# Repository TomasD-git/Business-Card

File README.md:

# Business-Card

> A custom dev board built inside a business card — NFC, e-paper display and 16 exposed GPIO pins.

---

## Features

- E-paper display — Configure once image stays
- NFC — tap to share Contact info, a URL, or any custom NFC
- 16 exposed GPIO pins — Connector makes it easy to use for another project
- No power design - Once flashed and configured, nfc works with no external power and image stays on e-paper screen

---

## How It Works

The Business Card is a fully custom PCB designed. The microcontroller drives both the e-paper display and the NFC IC over SPI/I2C, while the 16 GPIO pins are broken out along one edge for easy prototyping.

On power-up, the firmware initialises the display and NFC tag, can be configured, the e-paper holds whatever was last written without needing a continuous refresh.

---

## Schematic Overview

The schematic is split into four main blocks:

**MCU**: Core microcontroller, configuration of nfc and e-paper, GPIO pins   
**E-paper interface**: Has 8 exposed pins to solder an E-paper onto the PCB  
**NFC**: NFC IC with antenna matching network, presents as a standard NDEF tag  
**Power**: Power regulation with decoupling  

---

## PCB

Designed in KiCad, manufactured as a standard 2-layer board with PCBA. Gerber files and BOM are in the repo if you want to order your own.

---

<details>
  <summary>BOM</summary>

| Name | Purpose | Quantity | Total Cost (USD) | Link | Distributor |
|------|---------|----------|-----------------|------|-------------|
| locknut | secures the screen in place with M2 bolts | 1 | 4.88 | [Link](https://www.aliexpress.com/item/32963044301.html) | Aliexpress |
| PCB + PCBA | PCB with PCBA | 2 | 73.27 | [Link](https://jlcpcb.com) | jlcpcb |
| E-Paper, 2.13" | Screen to see my name | 1 | 12.44 | [Link](https://www.aliexpress.com/item/1005005183232092.html) | Aliexpress |

</details>

<details>
  <summary>For Future</summary>

## Planned improvements

**User interface**    
Change firmware so it could be configured with web or custom application.  

**Custom CAD**  
Some type of CAD to protect mcu.  

</details>

<details>
  <summary>License</summary>

### MIT License

**Copyright (c) [2026] [TomasD-git]**

Permission is hereby granted, free of charge, to any person obtaining a copy
of this software and associated documentation files (the "Software"), to deal
in the Software without restriction, including without limitation the rights
to use, copy, modify, merge, publish, distribute, sublicense, and/or sell
copies of the Software, and to permit persons to whom the Software is
furnished to do so, subject to the following conditions:

The above copyright notice and this permission notice shall be included in all
copies or substantial portions of the Software.

THE SOFTWARE IS PROVIDED "AS IS", WITHOUT WARRANTY OF ANY KIND, EXPRESS OR
IMPLIED, INCLUDING BUT NOT LIMITED TO THE WARRANTIES OF MERCHANTABILITY,
FITNESS FOR A PARTICULAR PURPOSE AND NONINFRINGEMENT. IN NO EVENT SHALL THE
AUTHORS OR COPYRIGHT HOLDERS BE LIABLE FOR ANY CLAIM, DAMAGES OR OTHER
LIABILITY, WHETHER IN AN ACTION OF CONTRACT, TORT OR OTHERWISE, ARISING FROM,
OUT OF OR IN CONNECTION WITH THE SOFTWARE OR THE USE OR OTHER DEALINGS IN THE
SOFTWARE.

</details>

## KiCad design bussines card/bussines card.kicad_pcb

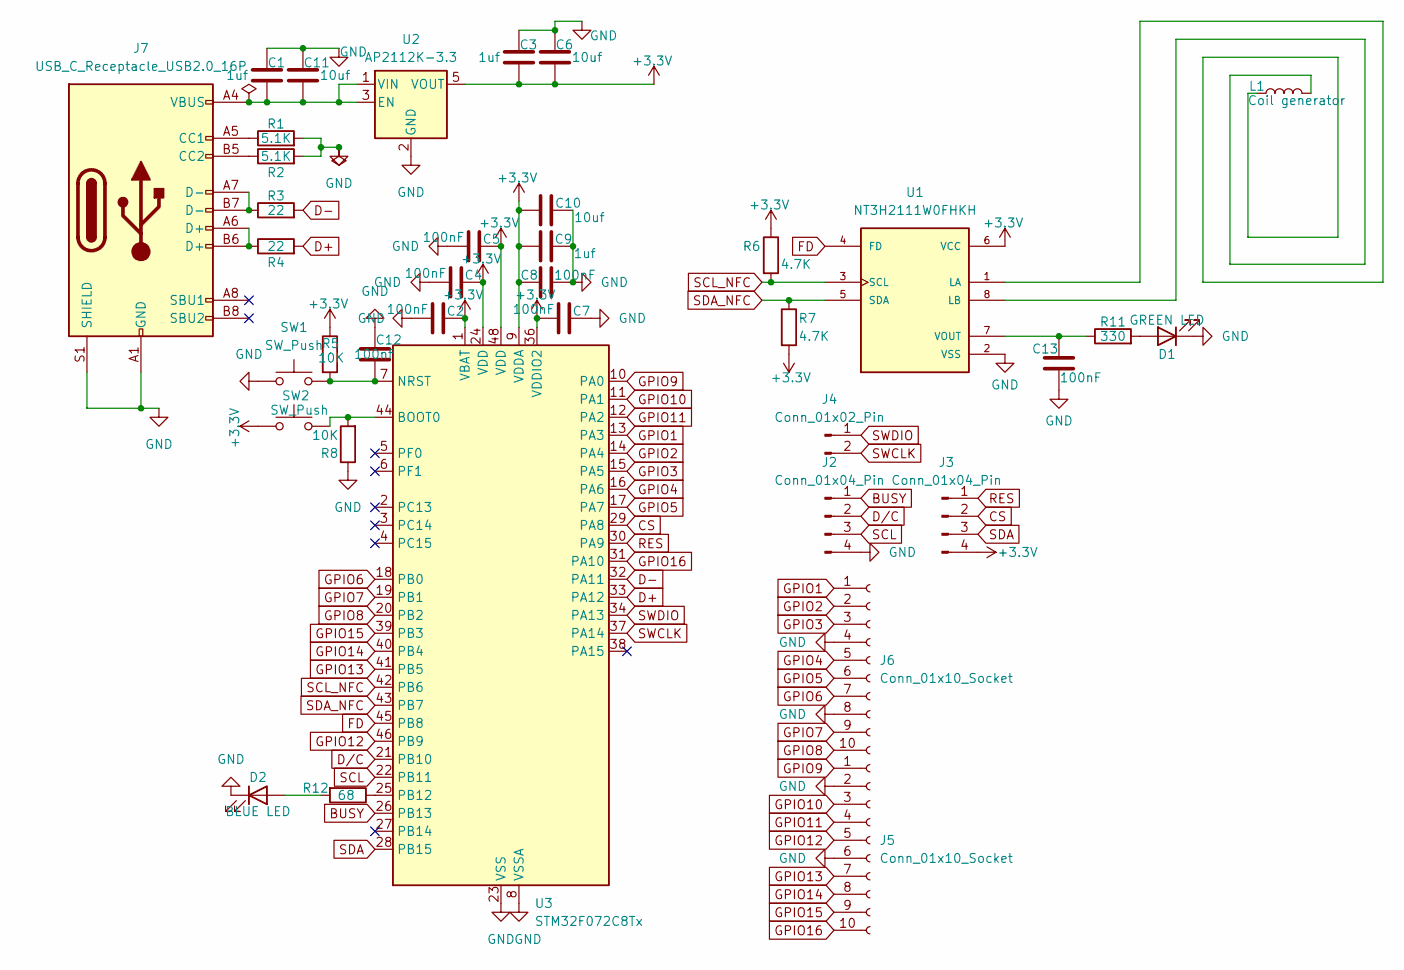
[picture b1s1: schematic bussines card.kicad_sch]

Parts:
C1, C3, C9: 1uf; C_0402_1005Metric
C2, C4, C5, C7, C8, C13: 100nF; C_0402_1005Metric
C6, C10, C11: 10uf; C_0603_1608Metric
C12: 100nf; C_0402_1005Metric
D1: GREEN LED; LED_0402_1005Metric
D2: BLUE LED; LED_0402_1005Metric
J2, J3: Conn_01x04_Pin; PinHeader_1x04_P2.54mm_Vertical
J4: Conn_01x02_Pin; PinHeader_1x02_P2.54mm_Vertical
J5, J6: Conn_01x10_Socket; PinSocket_1x10_P2.54mm_Vertical
J7: USB_C_Receptacle_USB2.0_16P; USB_C_Receptacle_XKB_U262-16XN-4BVC11
L1: Coil generator; COIL_GENERATOR
R1, R2: 5.1K; R_0402_1005Metric
R3, R4: 22; R_0402_1005Metric
R5, R8: 10K; R_0402_1005Metric
R6, R7: 4.7K; R_0402_1005Metric
R11: 330; R_0402_1005Metric
R12: 68; R_0402_1005Metric
SW1, SW2: SW_Push; SW_Push_1P1T_XKB_TS-1187A
U1: NT3H2111W0FHKH; QFN8P50_160X160X50L40X20N
U2: AP2112K-3.3; SOT-23-5
U3: STM32F072C8Tx; LQFP-48_7x7mm_P0.5mm

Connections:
+3.3V: C2.2, C3.2, C4.2, C5.2, C6.2, C7.1, C8.1, C9.1, C10.1, J3.4, R5.1, R6.1, R7.2, SW2.1, U1.6 (VCC), U2.5 (VOUT), U3.1 (VBAT), U3.9 (VDDA), U3.24 (VDD), U3.36 (VDDIO2), U3.48 (VDD); also elsewhere on the board
BUSY: J2.1, U3.26 (PB13)
CS: J3.2, U3.29 (PA8)
D+: R4.2, U3.33 (PA12)
D-: R3.2, U3.32 (PA11)
D/C: J2.2, U3.21 (PB10)
FD: U1.4 (FD), U3.45 (PB8)
GND: C1.1, C2.1, C3.1, C4.1, C5.1, C6.1, C7.2, C8.2, C9.2, C10.2, C11.1, C12.1, C13.1, D1.1 (K), D2.1 (K), J2.4, J5.2, J5.6, J6.4, J6.8, J7.A1 (GND), J7.A12 (GND), J7.B1 (GND), J7.B12 (GND), J7.S1 (SHIELD), R1.2, R2.2, R8.1, SW1.1, U1.2 (VSS), U2.2 (GND), U3.8 (VSSA), U3.23 (VSS), U3.35 (VSS), U3.47 (VSS); also elsewhere on the board
GPIO1: J6.1, U3.13 (PA3)
GPIO2: J6.2, U3.14 (PA4)
GPIO3: J6.3, U3.15 (PA5)
GPIO4: J6.5, U3.16 (PA6)
GPIO5: J6.6, U3.17 (PA7)
GPIO6: J6.7, U3.18 (PB0)
GPIO7: J6.9, U3.19 (PB1)
GPIO8: J6.10, U3.20 (PB2)
GPIO9: J5.1, U3.10 (PA0)
GPIO10: J5.3, U3.11 (PA1)
GPIO11: J5.4, U3.12 (PA2)
GPIO12: J5.5, U3.46 (PB9)
GPIO13: J5.7, U3.41 (PB5)
GPIO14: J5.8, U3.40 (PB4)
GPIO15: J5.9, U3.39 (PB3)
GPIO16: J5.10, U3.31 (PA10)
unnamed: D1.2 (A), R11.2
unnamed: D2.2 (A), R12.2
unnamed: J7.A5 (CC1), R1.1
unnamed: J7.B5 (CC2), R2.1
unnamed: J7.A6 (D+), J7.B6 (D+), R4.1
unnamed: J7.A7 (D-), J7.B7 (D-), R3.1
unnamed: L1.1, U1.1 (LA)
unnamed: L1.2, U1.8 (LB)
unnamed: C13.2, R11.1, U1.7 (VOUT)
unnamed: C1.2, C11.2, J7.A4 (VBUS), J7.A9 (VBUS), J7.B4 (VBUS), J7.B9 (VBUS), U2.1 (VIN), U2.3 (EN)
unnamed 34: R8.2, SW2.2, U3.44 (BOOT0); also elsewhere on the board
unnamed 35: C12.2, R5.2, SW1.2, U3.7 (NRST); also elsewhere on the board
unnamed: R12.1, U3.25 (PB12)
RES: J3.1, U3.30 (PA9)
SCL: J2.3, U3.22 (PB11)
SCL_NFC: R6.2, U1.3 (SCL), U3.42 (PB6)
SDA: J3.3, U3.28 (PB15)
SDA_NFC: R7.1, U1.5 (SDA), U3.43 (PB7)
SWCLK: J4.2, U3.37 (PA14)
SWDIO: J4.1, U3.34 (PA13)

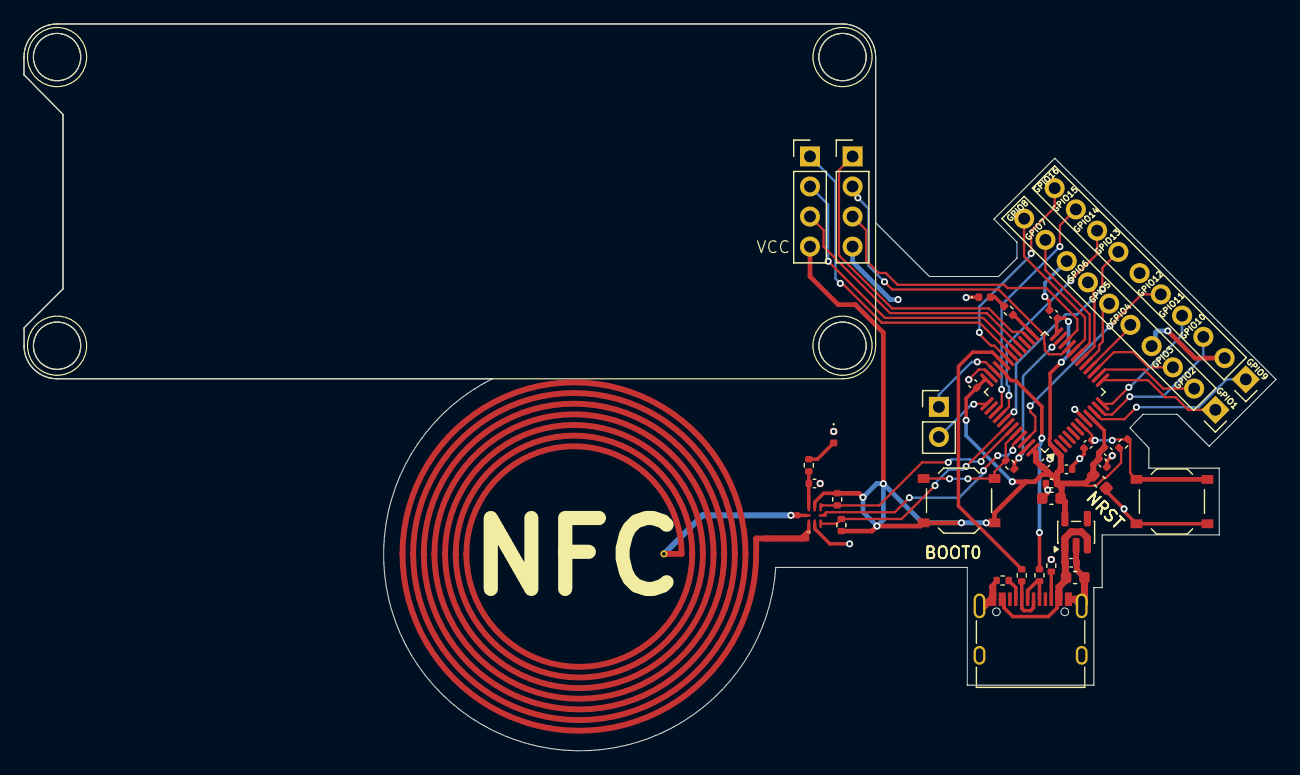
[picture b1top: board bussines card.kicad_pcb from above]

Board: 2 copper layers, 105.9 x 61.4 mm, 37 parts (0 on the bottom side), 44 nets.

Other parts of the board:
BOOT0: SW_Push; SW_Push_1P1T_XKB_TS-1187A
NRST: SW_Push; SW_Push_1P1T_XKB_TS-1187A

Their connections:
+3.3V: BOOT0.1; also elsewhere on the board
GND: NRST.1; also elsewhere on the board
unnamed 34: BOOT0.2; also elsewhere on the board
unnamed 35: NRST.2; also elsewhere on the board

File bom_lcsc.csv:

Designator,Footprint,Quantity,Value,LCSC Part #
"BOOT0, NRST",SW_Push_1P1T_XKB_TS-1187A,2,SW_Push,C318884
"C1, C3, C9",0402,3,1uF,C52923
"C10, C11, C6",0603,3,10uF,C19702
"C12, C13, C2, C4, C5, C7, C8",0402,7,100nF,C1525
D1,0402,1,GREEN LED,C74338
D2,0402,1,BLUE LED,C131223
"J2, J3",PinHeader_1x04_P2.54mm_Vertical,2,Conn_01x04_Pin,
J4,PinHeader_1x02_P2.54mm_Vertical,1,Conn_01x02_Pin,
"J5, J6",PinSocket_1x10_P2.54mm_Vertical,2,Conn_01x10_Socket,
J7,USB_C_Receptacle_XKB_U262-16XN-4BVC11,1,USB_C_Receptacle_USB2.0_16P,C319148
L1,COIL_GENERATOR,1,L,
"R1, R2",0402,2,5.1K,C25905
R11,0402,1,330,C25104
R12,0402,1,68,C25758
"R3, R4",0402,2,22,C25092
"R5, R8",0402,2,10K,C25744
"R6, R7",0402,2,4.7K,C25900
U1,QFN8P50_160X160X50L40X20N,1,NT3H2111W0FHKH,C710403
U2,SOT-23-5,1,AP2112K-3.3,C51118
U3,LQFP-48_7x7mm_P0.5mm,1,STM32F072C8Tx,C80488

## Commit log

2026-05-11 Add firmware flashing instructions to README
    Added instructions for flashing STM32 firmware via USB-C.
2026-05-11 added main firmware files
2026-05-11 added KiCad files
2026-05-12 added main files for PCBA
2026-05-12 added binary firmware
2026-05-12 Revise README for clarity and additional details
    Updated the README to provide a clearer description and detailed features of the Business Card project, including how it works, schematic overview, PCB design, BOM, planned improvements, and license 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
2026-05-12 Format README.md for consistency and clarity
